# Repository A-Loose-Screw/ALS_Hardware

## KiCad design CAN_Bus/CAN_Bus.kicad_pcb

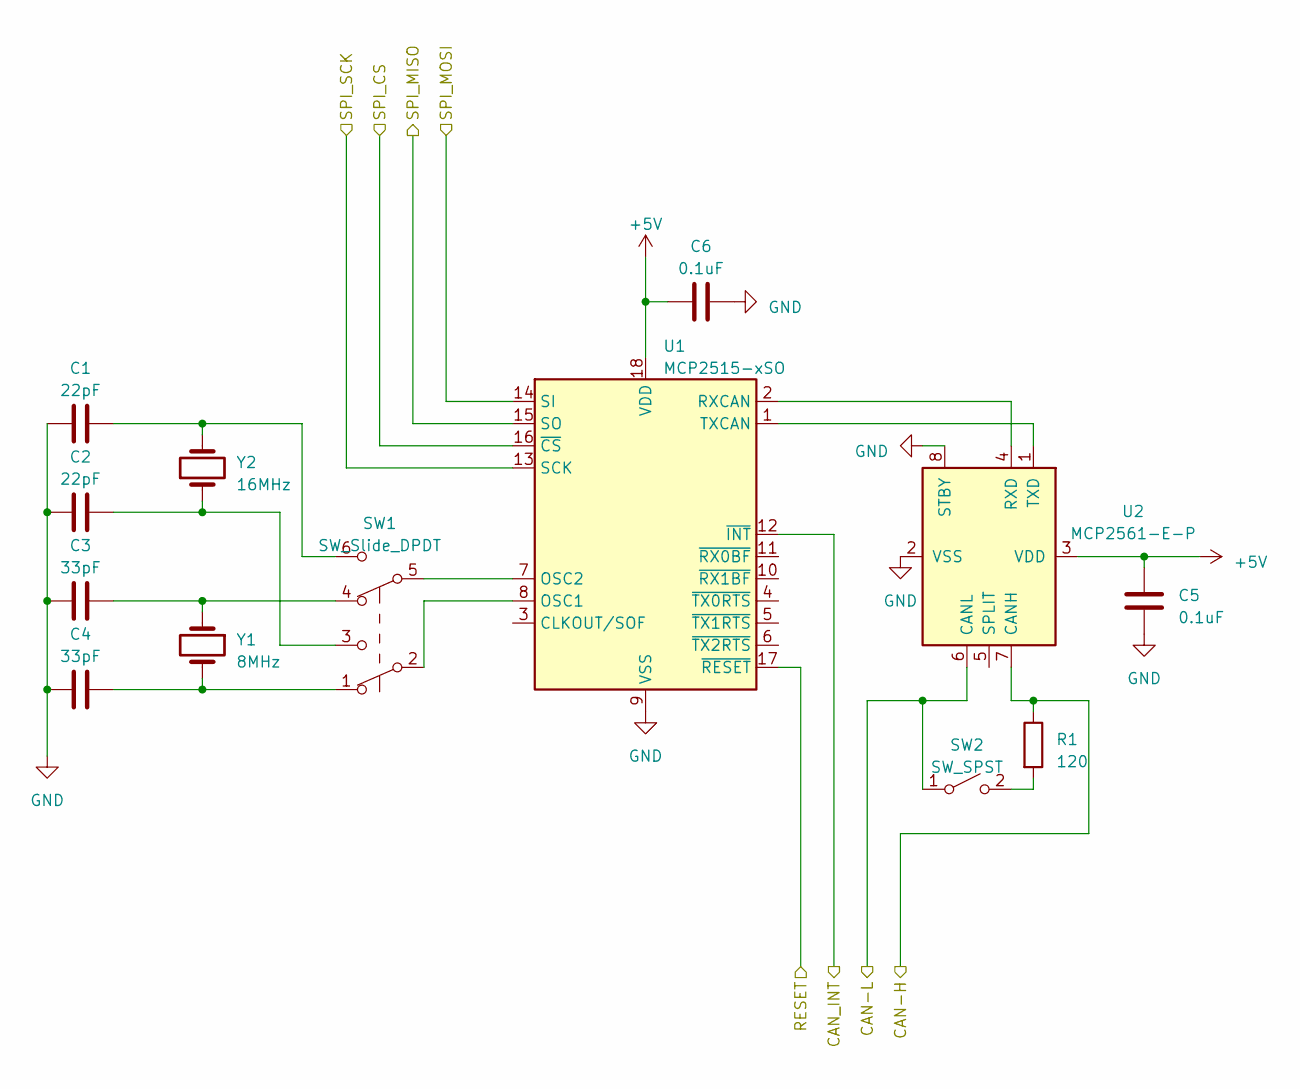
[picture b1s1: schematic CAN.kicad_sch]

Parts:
C1, C2: 22pF; C_Disc_D5.0mm_W2.5mm_P5.00mm
C3, C4: 33pF; C_Disc_D5.0mm_W2.5mm_P5.00mm
C5, C6: 0.1uF; C_Disc_D5.0mm_W2.5mm_P5.00mm
R1: 120; R_2512_6332Metric
SW1: SW_Slide_DPDT; SW_CuK_JS202011CQN_DPDT_Straight
SW2: SW_SPST; SW_DIP_SPSTx01_Slide_9.78x4.72mm_W7.62mm_P2.54mm
U1: MCP2515-xSO; SOIC-18W_7.5x11.6mm_P1.27mm
U2: MCP2561-E-P; DIP-8_W7.62mm
Y1: 8MHz; Crystal_HC49-4H_Vertical
Y2: 16MHz; Crystal_HC49-4H_Vertical

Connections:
/CAN/5v: C5.1, C6.1, U1.18 (VDD), U2.3 (VDD); also elsewhere on the board
/CAN/CAN-H: R1.1, U2.7 (CANH); also elsewhere on the board
/CAN/CAN-L: SW2.1 (A), U2.6 (CANL); also elsewhere on the board
/CAN/CAN_INT: U1.12 (~INT); also elsewhere on the board
/CAN/RESET: U1.17 (~RESET); also elsewhere on the board
/CAN/SPI_CS: U1.16 (~CS); also elsewhere on the board
/CAN/SPI_MISO: U1.15 (SO); also elsewhere on the board
/CAN/SPI_MOSI: U1.14 (SI); also elsewhere on the board
/CAN/SPI_SCK: U1.13 (SCK); also elsewhere on the board
/CAN/gnd: C1.1, C2.1, C3.1, C4.1, C5.2, C6.2, U1.9 (VSS), U2.2 (VSS), U2.8 (STBY); also elsewhere on the board
unnamed: C1.2, SW1.6 (C), Y2.2
unnamed: C2.2, SW1.3 (C), Y2.1
unnamed: C3.2, SW1.4 (A), Y1.1
unnamed: C4.2, SW1.1 (A), Y1.2
unnamed: R1.2, SW2.2 (B)
unnamed: SW1.2 (B), U1.8 (OSC1)
unnamed: SW1.5 (B), U1.7 (OSC2)
unnamed: U1.2 (RXCAN), U2.4 (RXD)
unnamed: U1.1 (TXCAN), U2.1 (TXD)

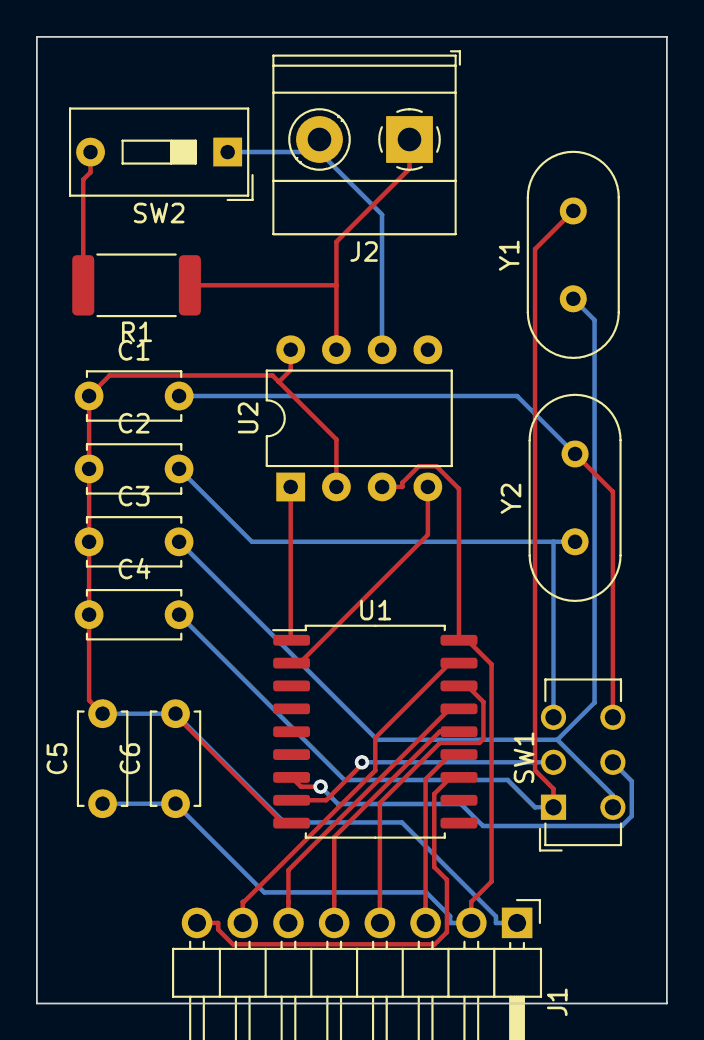
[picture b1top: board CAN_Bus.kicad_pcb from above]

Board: 2 copper layers, 35.0 x 53.7 mm, 15 parts (0 on the bottom side), 19 nets.

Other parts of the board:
J1: Conn_01x08; PinHeader_1x08_P2.54mm_Horizontal
J2: Screw_Terminal_01x02; TerminalBlock_Phoenix_MKDS-1,5-2_1x02_P5.00mm_Horizontal

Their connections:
/CAN/5v: J1.2; also elsewhere on the board
/CAN/CAN-H: J2.1; also elsewhere on the board
/CAN/CAN-L: J2.2; also elsewhere on the board
/CAN/CAN_INT: J1.8; also elsewhere on the board
/CAN/RESET: J1.7; also elsewhere on the board
/CAN/SPI_CS: J1.4; also elsewhere on the board
/CAN/SPI_MISO: J1.6; also elsewhere on the board
/CAN/SPI_MOSI: J1.5; also elsewhere on the board
/CAN/SPI_SCK: J1.3; also elsewhere on the board
/CAN/gnd: J1.1; also elsewhere on the board

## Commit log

2023-03-07 finalized schematic (not pcb)
2023-03-07 Create LICENSE
2023-03-11 Added example circuit board
